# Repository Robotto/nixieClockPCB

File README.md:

[ibom](https://htmlpreview.github.io/?https://github.com/robotto/nixieClockPCB/blob/master/bom/ibom.html)
[kicanvas](https://kicanvas.org/?github=https://github.com/Robotto/nixieClockPCB)

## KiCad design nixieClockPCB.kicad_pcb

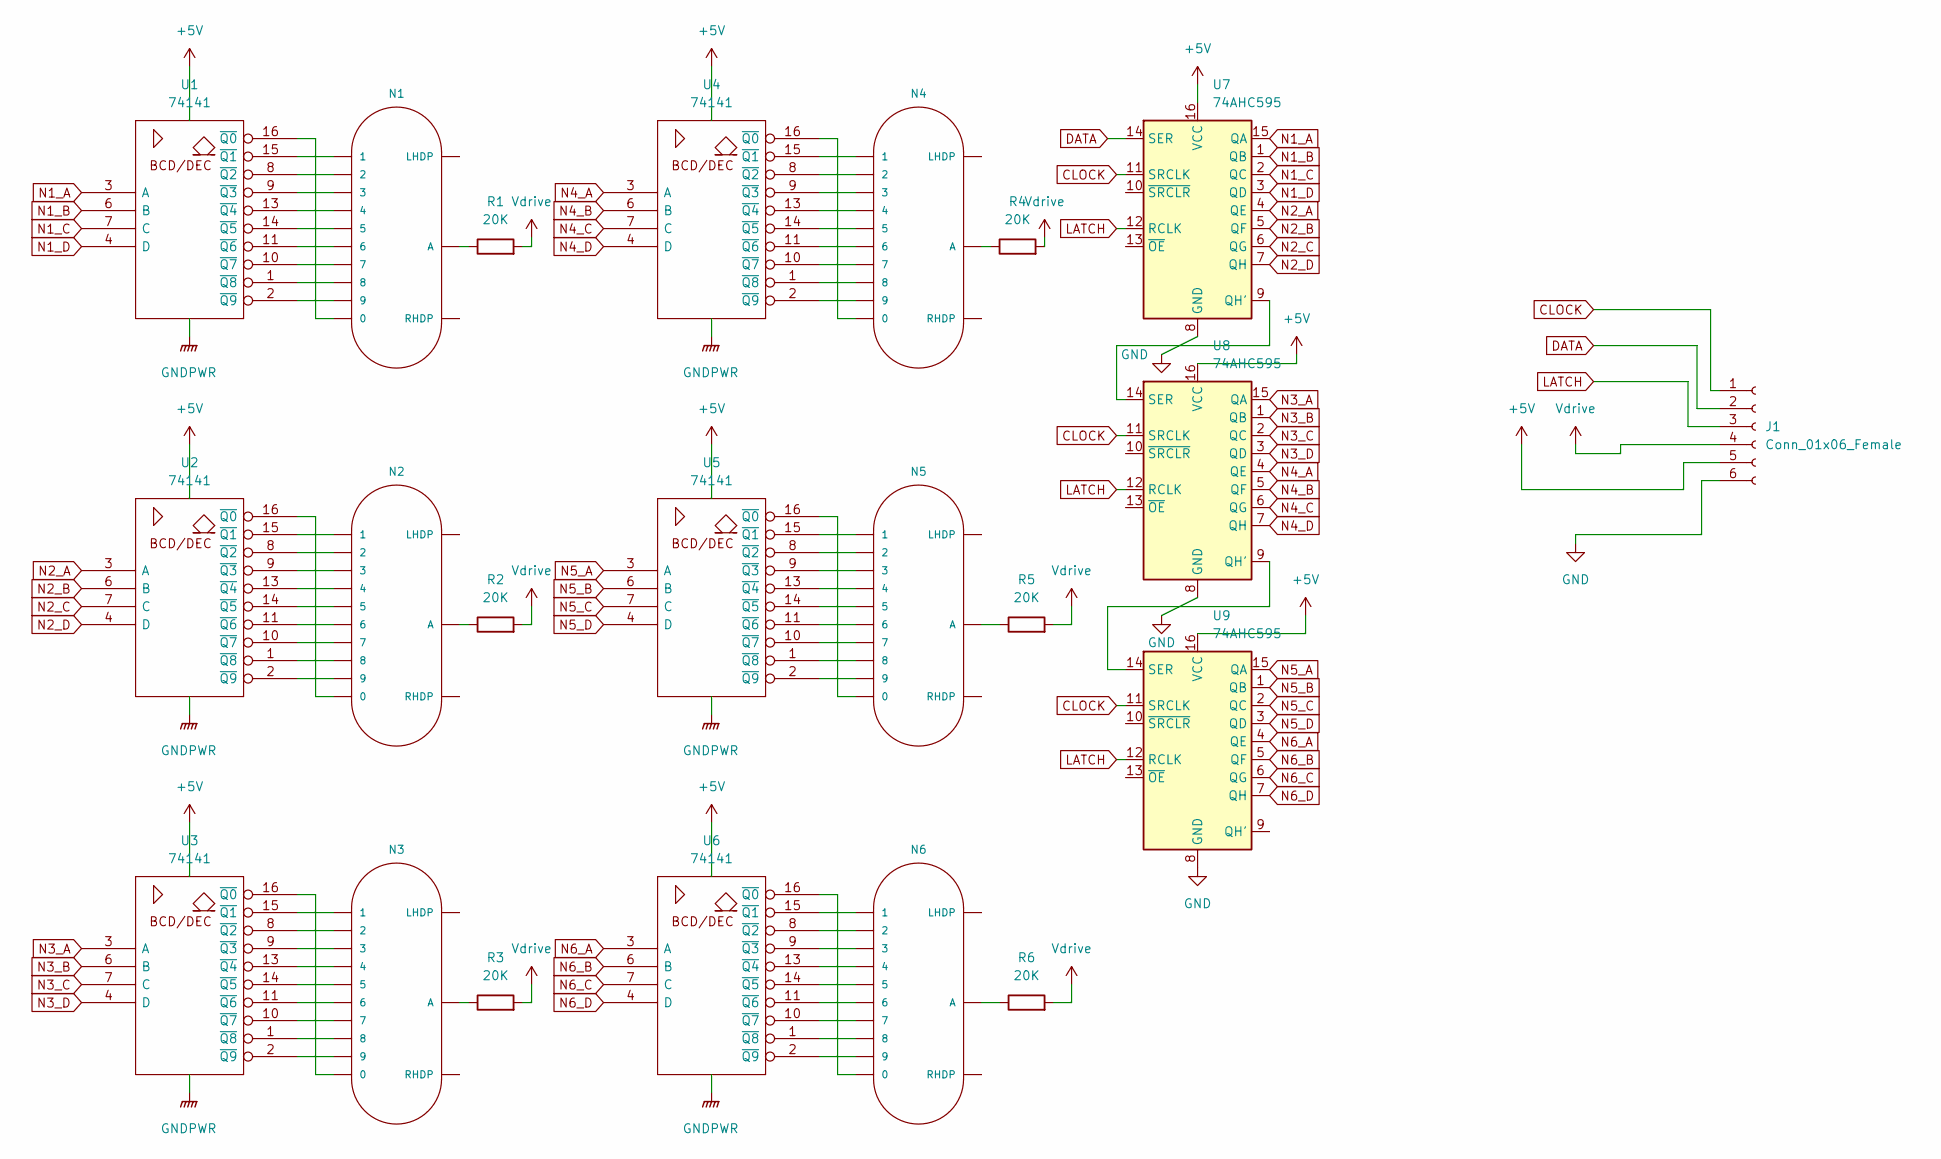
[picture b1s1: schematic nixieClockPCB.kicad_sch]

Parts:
J1: Conn_01x06_Female; PinHeader_1x06_P1.27mm_Vertical
N1, N2, N3, N4, N5, N6: IN-16; nixies-us-IN-16
R1, R2, R3, R4, R5, R6: 20K; R_Axial_DIN0414_L11.9mm_D4.5mm_P15.24mm_Horizontal
U1, U2, U3, U4, U5, U6: 74141; DIP-16_W7.62mm
U7, U8, U9: 74AHC595; nixiemisc-SOIC16-5.3MM

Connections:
+5V: J1.5, U1.5 (VCC), U2.5 (VCC), U3.5 (VCC), U4.5 (VCC), U5.5 (VCC), U6.5 (VCC), U7.16 (VCC), U8.16 (VCC), U9.16 (VCC)
CLOCK: J1.1, U7.11 (SRCLK), U8.11 (SRCLK), U9.11 (SRCLK)
DATA: J1.2, U7.14 (SER)
LATCH: J1.3, U7.12 (RCLK), U8.12 (RCLK), U9.12 (RCLK)
N1_A: U1.3 (A), U7.15 (QA)
N1_B: U1.6 (B), U7.1 (QB)
N1_C: U1.7 (C), U7.2 (QC)
N1_D: U1.4 (D), U7.3 (QD)
N2_A: U2.3 (A), U7.4 (QE)
N2_B: U2.6 (B), U7.5 (QF)
N2_C: U2.7 (C), U7.6 (QG)
N2_D: U2.4 (D), U7.7 (QH)
N3_A: U3.3 (A), U8.15 (QA)
N3_B: U3.6 (B), U8.1 (QB)
N3_C: U3.7 (C), U8.2 (QC)
N3_D: U3.4 (D), U8.3 (QD)
N4_A: U4.3 (A), U8.4 (QE)
N4_B: U4.6 (B), U8.5 (QF)
N4_C: U4.7 (C), U8.6 (QG)
N4_D: U4.4 (D), U8.7 (QH)
N5_A: U5.3 (A), U9.15 (QA)
N5_B: U5.6 (B), U9.1 (QB)
N5_C: U5.7 (C), U9.2 (QC)
N5_D: U5.4 (D), U9.3 (QD)
N6_A: U6.3 (A), U9.4 (QE)
N6_B: U6.6 (B), U9.5 (QF)
N6_C: U6.7 (C), U9.6 (QG)
N6_D: U6.4 (D), U9.7 (QH)
unnamed: N1.0, U1.16 (~Q0)
unnamed: N1.1, U1.15 (~Q1)
unnamed: N1.2, U1.8 (~Q2)
unnamed: N1.3, U1.9 (~Q3)
unnamed: N1.4, U1.13 (~Q4)
unnamed: N1.5, U1.14 (~Q5)
unnamed: N1.6, U1.11 (~Q6)
unnamed: N1.7, U1.10 (~Q7)
unnamed: N1.8, U1.1 (~Q8)
unnamed: N1.9, U1.2 (~Q9)
unnamed: N1.A, R1.1
unnamed: N2.0, U2.16 (~Q0)
unnamed: N2.1, U2.15 (~Q1)
unnamed: N2.2, U2.8 (~Q2)
unnamed: N2.3, U2.9 (~Q3)
unnamed: N2.4, U2.13 (~Q4)
unnamed: N2.5, U2.14 (~Q5)
unnamed: N2.6, U2.11 (~Q6)
unnamed: N2.7, U2.10 (~Q7)
unnamed: N2.8, U2.1 (~Q8)
unnamed: N2.9, U2.2 (~Q9)
unnamed: N2.A, R2.1
unnamed: N3.0, U3.16 (~Q0)
unnamed: N3.1, U3.15 (~Q1)
unnamed: N3.2, U3.8 (~Q2)
unnamed: N3.3, U3.9 (~Q3)
unnamed: N3.4, U3.13 (~Q4)
unnamed: N3.5, U3.14 (~Q5)
unnamed: N3.6, U3.11 (~Q6)
unnamed: N3.7, U3.10 (~Q7)
unnamed: N3.8, U3.1 (~Q8)
unnamed: N3.9, U3.2 (~Q9)
unnamed: N3.A, R3.1
unnamed: N4.0, U4.16 (~Q0)
unnamed: N4.1, U4.15 (~Q1)
unnamed: N4.2, U4.8 (~Q2)
unnamed: N4.3, U4.9 (~Q3)
unnamed: N4.4, U4.13 (~Q4)
unnamed: N4.5, U4.14 (~Q5)
unnamed: N4.6, U4.11 (~Q6)
unnamed: N4.7, U4.10 (~Q7)
unnamed: N4.8, U4.1 (~Q8)
unnamed: N4.9, U4.2 (~Q9)
unnamed: N4.A, R4.1
unnamed: N5.0, U5.16 (~Q0)
unnamed: N5.1, U5.15 (~Q1)
unnamed: N5.2, U5.8 (~Q2)
unnamed: N5.3, U5.9 (~Q3)
unnamed: N5.4, U5.13 (~Q4)
unnamed: N5.5, U5.14 (~Q5)
unnamed: N5.6, U5.11 (~Q6)
unnamed: N5.7, U5.10 (~Q7)
unnamed: N5.8, U5.1 (~Q8)
unnamed: N5.9, U5.2 (~Q9)
unnamed: N5.A, R5.1
unnamed: N6.0, U6.16 (~Q0)
unnamed: N6.1, U6.15 (~Q1)
unnamed: N6.2, U6.8 (~Q2)
unnamed: N6.3, U6.9 (~Q3)
unnamed: N6.4, U6.13 (~Q4)
unnamed: N6.5, U6.14 (~Q5)
unnamed: N6.6, U6.11 (~Q6)
unnamed: N6.7, U6.10 (~Q7)
unnamed: N6.8, U6.1 (~Q8)
unnamed: N6.9, U6.2 (~Q9)
unnamed: N6.A, R6.1
unnamed: U7.9 (QH'), U8.14 (SER)
unnamed: U8.9 (QH'), U9.14 (SER)
Vdrive: J1.4, R1.2, R2.2, R3.2, R4.2, R5.2, R6.2

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
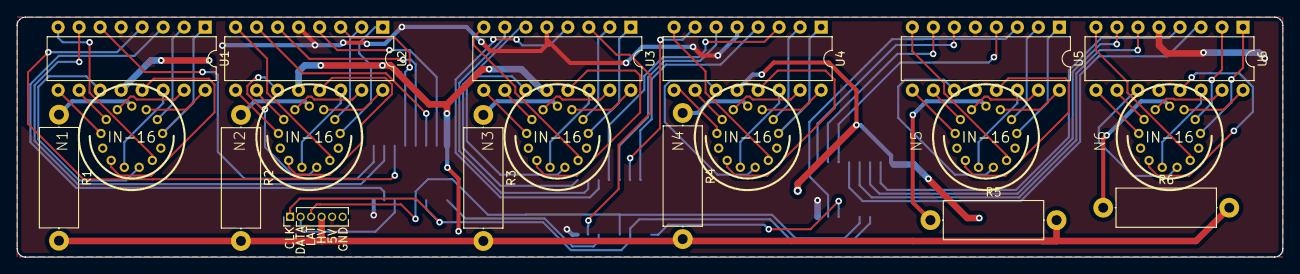
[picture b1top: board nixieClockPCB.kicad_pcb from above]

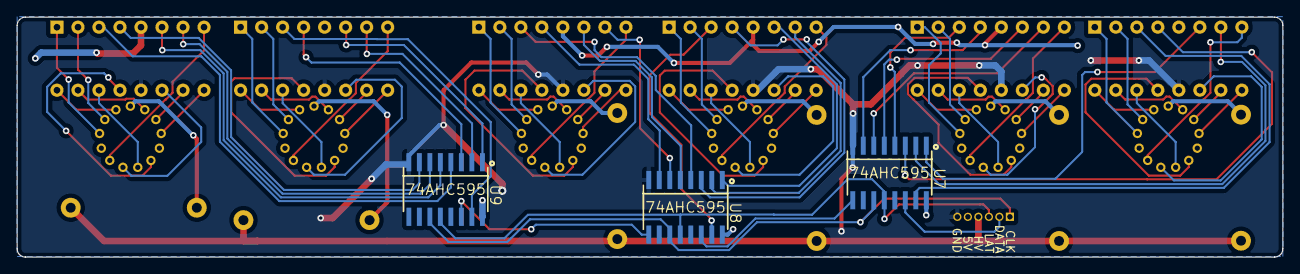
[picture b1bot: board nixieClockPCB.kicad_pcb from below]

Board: 2 copper layers, 153.0 x 29.0 mm, 22 parts (3 on the bottom side), 98 nets.

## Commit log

2023-12-21 init
2023-12-22 layout moving.
2023-12-24 First routing iteration done
2023-12-24 Added input
2023-12-25 added input jumper
2023-12-25 More routing, and gerber generation
2023-12-25 generated ibom
2023-12-25 gerber zip
2023-12-25 Create README.md
    Doc links
2023-12-25 readme
2023-12-25 do these dox work?
2023-12-25 meh....
